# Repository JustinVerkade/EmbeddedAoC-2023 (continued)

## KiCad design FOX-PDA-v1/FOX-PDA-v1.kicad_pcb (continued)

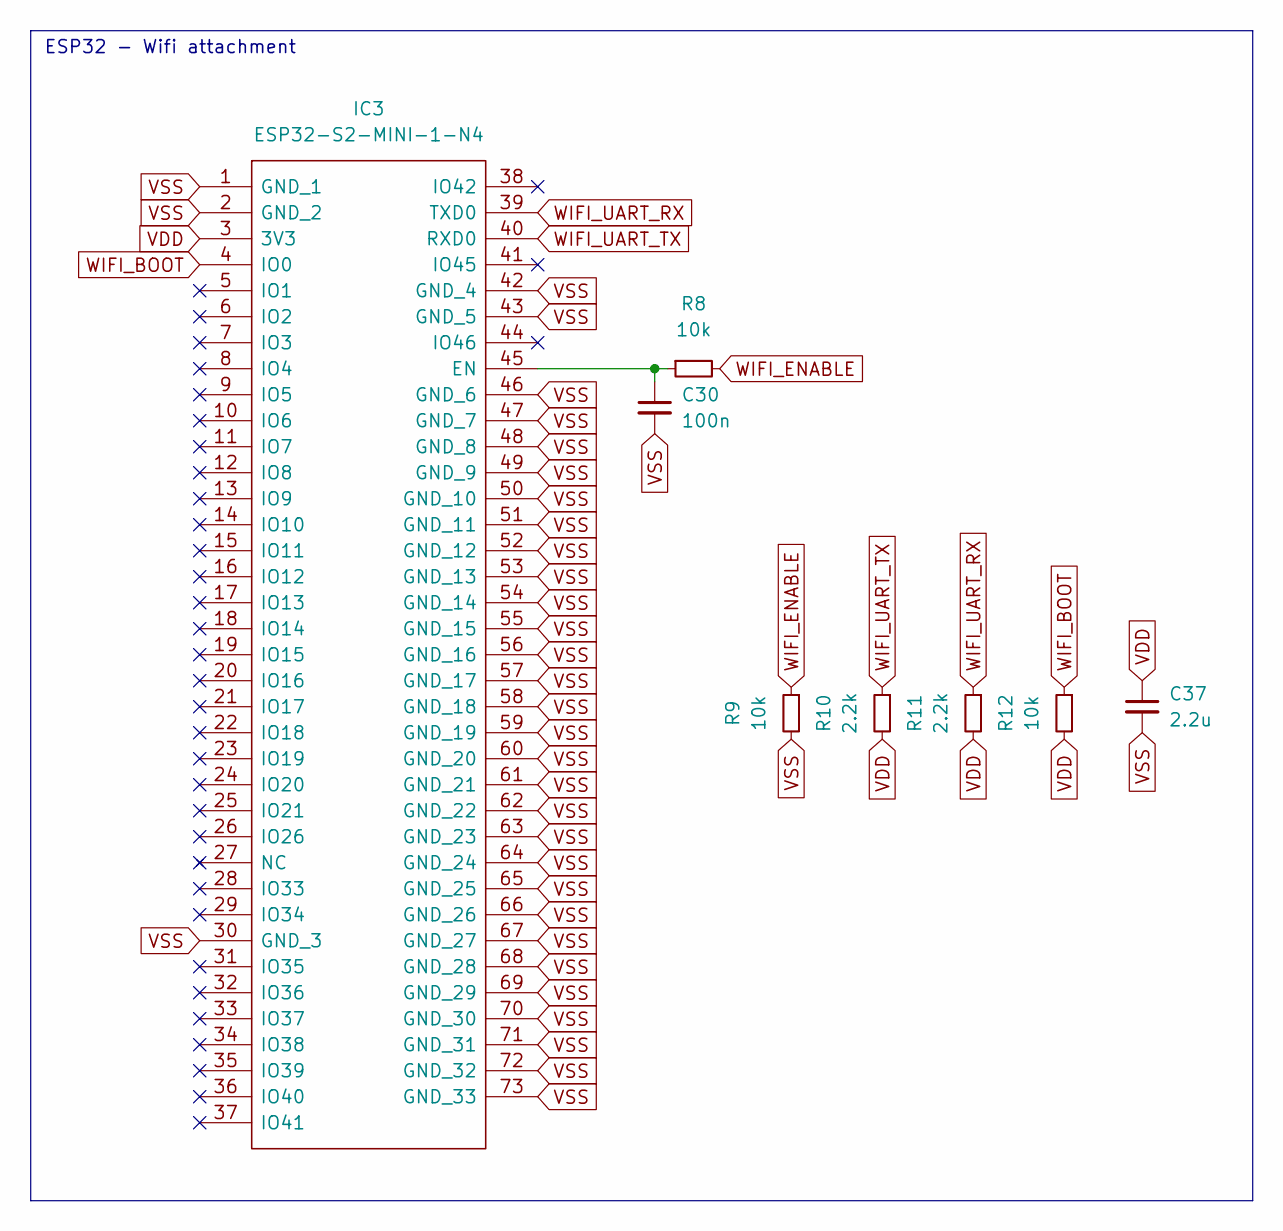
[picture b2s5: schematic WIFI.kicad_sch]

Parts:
C30: 100n; C_0402_1005Metric
C37: 2.2u; C_0603_1608Metric
IC3: ESP32-S2-MINI-1-N4; ESP32S2MINI1N4; Mouser Part Number 356-ESP32-S2-MINI-1
R8, R9, R12: 10k; R_0402_1005Metric
R10, R11: 2.2k; R_0402_1005Metric

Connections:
unnamed: C30.1, IC3.45 (EN), R8.1
VDD: C37.1, IC3.3 (3V3), R10.2, R11.2, R12.2; also elsewhere on the board
VSS: C30.2, C37.2, IC3.1 (GND_1), IC3.2 (GND_2), IC3.30 (GND_3), IC3.42 (GND_4), IC3.43 (GND_5), IC3.46 (GND_6), IC3.47 (GND_7), IC3.48 (GND_8), IC3.49 (GND_9), IC3.50 (GND_10), IC3.51 (GND_11), IC3.52 (GND_12), IC3.53 (GND_13), IC3.54 (GND_14), IC3.55 (GND_15), IC3.56 (GND_16), IC3.57 (GND_17), IC3.58 (GND_18), IC3.59 (GND_19), IC3.60 (GND_20), IC3.61 (GND_21), IC3.62 (GND_22), IC3.63 (GND_23), IC3.64 (GND_24), IC3.65 (GND_25), IC3.66 (GND_26), IC3.67 (GND_27), IC3.68 (GND_28), IC3.69 (GND_29), IC3.70 (GND_30), IC3.71 (GND_31), IC3.72 (GND_32), IC3.73 (GND_33), R9.2; also elsewhere on the board
WIFI_BOOT: IC3.4 (IO0), R12.1
WIFI_ENABLE: R8.2, R9.1; also elsewhere on the board
WIFI_UART_RX: IC3.39 (TXD0), R11.1; also elsewhere on the board
WIFI_UART_TX: IC3.40 (RXD0), R10.1; also elsewhere on the board

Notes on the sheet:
ESP32 - Wifi attachment

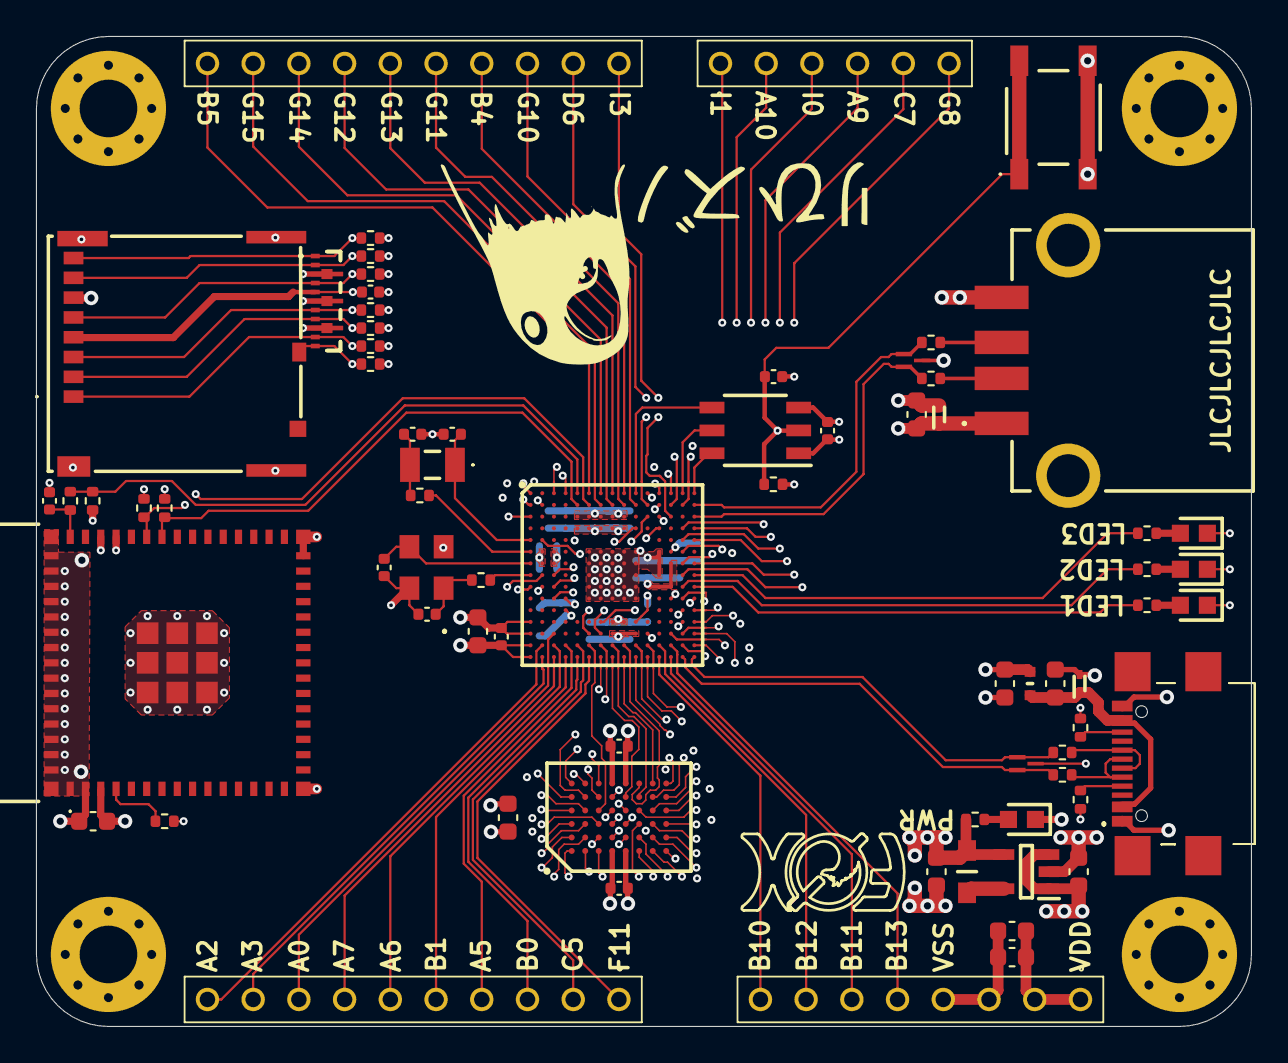
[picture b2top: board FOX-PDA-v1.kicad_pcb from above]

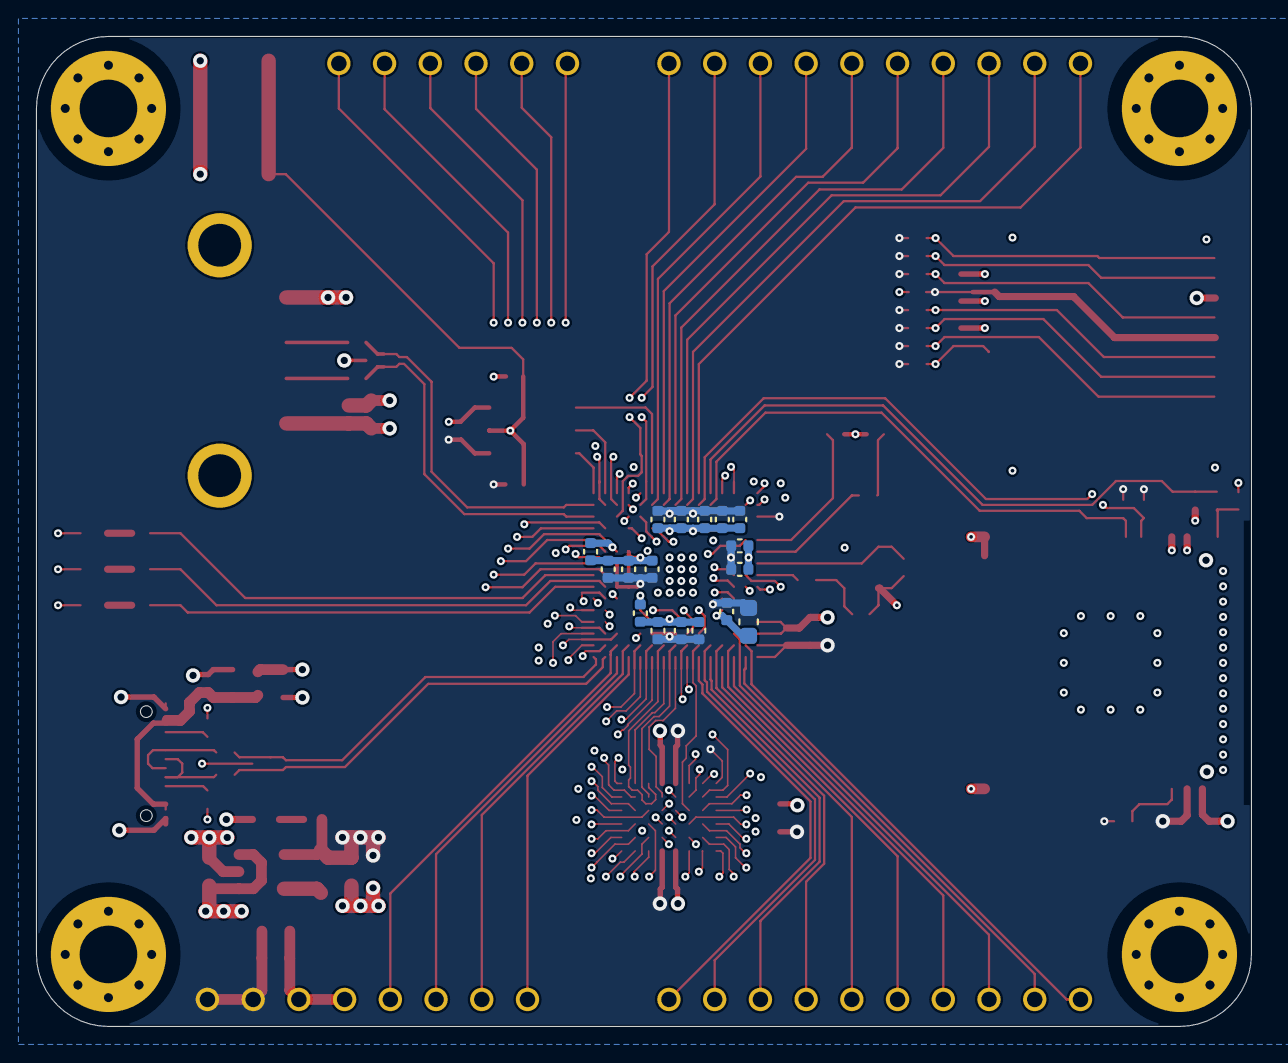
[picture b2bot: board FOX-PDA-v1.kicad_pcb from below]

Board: 6 copper layers, 67.5 x 55.0 mm, 93 parts (17 on the bottom side), 119 nets.

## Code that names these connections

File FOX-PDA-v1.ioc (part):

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Mcu.Name=STM32F745I(E-G)Kx
Mcu.Package=UFBGA176
Mcu.UserName=STM32F745IGKx
PA0/WKUP.Signal=ADCx_IN0
PA10.Signal=GPIO_Input
PA11.Mode=Host_Only
PA11.Signal=USB_OTG_FS_DM
PA12.Mode=Host_Only
PA12.Signal=USB_OTG_FS_DP
PA13.Mode=Trace_Asynchronous_SW
PA13.Signal=SYS_JTMS-SWDIO
PA14.Mode=Trace_Asynchronous_SW
PA14.Signal=SYS_JTCK-SWCLK
PA15.GPIOParameters=GPIO_Label
PA15.GPIO_Label=SDMMC_SW
PA15.Signal=GPIO_Input
PA2.Signal=ADCx_IN2
PA3.Signal=GPIO_Input
PA5.Signal=GPIO_Input
PA6.Signal=GPIO_Input
PA7.Signal=GPIO_Input
PA9.Signal=GPIO_Input
PB0.Signal=GPIO_Input
PB1.Signal=GPIO_Input
PB10.Signal=GPIO_Input
PB11.Signal=GPIO_Input
PB12.Signal=GPIO_Input
PB13.Signal=GPIO_Input
PB14.Mode=Device_Only_FS
PB14.Signal=USB_OTG_HS_DM
PB15.Mode=Device_Only_FS
PB15.Signal=USB_OTG_HS_DP
PB3.Mode=Trace_Asynchronous_SW
PB3.Signal=SYS_JTDO-SWO
PB4.Signal=GPIO_Input
PB5.Signal=GPIO_Input
PB6.GPIOParameters=GPIO_Label
PB6.GPIO_Label=WIFI_UART_TX
PB6.Mode=Asynchronous
PB6.Signal=USART1_TX
PB7.GPIOParameters=GPIO_Label
PB7.GPIO_Label=WIFI_UART_RX
PB7.Mode=Asynchronous
PB7.Signal=USART1_RX
PB8.GPIOParameters=GPIO_Label
PB8.GPIO_Label=WIFI_ENABLE
PB8.Signal=GPIO_Output
PC10.Signal=SDMMC1_D2
PC11.Signal=SDMMC1_D3
PC12.Mode=SD_1_bit
PC12.Signal=SDMMC1_CK
PC14/OSC32_IN.Mode=LSE-External-Oscillator
PC14/OSC32_IN.Signal=RCC_OSC32_IN
PC15/OSC32_OUT.Mode=LSE-External-Oscillator
PC15/OSC32_OUT.Signal=RCC_OSC32_OUT
PC5.Signal=GPIO_Input
PC6.GPIOParameters=GPIO_Label
PC6.GPIO_Label=LED3
PC6.Signal=GPIO_Output
PC7.Signal=GPIO_Input
PC8.Mode=SD_1_bit
PC8.Signal=SDMMC1_D0
PC9.Signal=SDMMC1_D1
PD0.Signal=FMC_D2_DA2
PD1.Signal=FMC_D3_DA3
PD10.Signal=FMC_D15_DA15
PD11.Signal=FMC_A16_CLE
PD12.Signal=FMC_A17_ALE
PD13.Signal=FMC_A18
PD14.Signal=FMC_D0_DA0
PD15.Signal=FMC_D1_DA1
PD2.Mode=SD_1_bit
PD2.Signal=SDMMC1_CMD
PD4.Signal=FMC_NOE
PD5.Signal=FMC_NWE
PD6.Signal=GPIO_Input
PD7.Mode=NorPsramChipSelect1_1
PD7.Signal=FMC_NE1
PD8.Signal=FMC_D13_DA13
PD9.Signal=FMC_D14_DA14
PE0.Signal=FMC_NBL0
PE1.Signal=FMC_NBL1
PE10.Signal=FMC_D7_DA7
PE11.Signal=FMC_D8_DA8
PE12.Signal=FMC_D9_DA9
PE13.Signal=FMC_D10_DA10
PE14.Signal=FMC_D11_DA11
PE15.Signal=FMC_D12_DA12
PE3.Signal=FMC_A19
PE4.Signal=FMC_A20
PE5.Signal=FMC_A21
PE7.Signal=FMC_D4_DA4
PE8.Signal=FMC_D5_DA5
PE9.Signal=FMC_D6_DA6
PF0.Signal=FMC_A0
PF1.Signal=FMC_A1
PF11.Signal=GPIO_Input
PF12.Signal=FMC_A6
PF13.Signal=FMC_A7
PF14.Signal=FMC_A8
PF15.Signal=FMC_A9
PF2.Signal=FMC_A2
PF3.Signal=FMC_A3
PF4.Signal=FMC_A4
PF5.Signal=FMC_A5
PF7.GPIOParameters=GPIO_Label
PF7.GPIO_Label=STATUS_LED
PF7.Signal=S_TIM11_CH1
PG0.Signal=FMC_A10
PG1.Signal=FMC_A11
PG10.Signal=GPIO_Input
PG11.Signal=GPIO_Input
PG12.Signal=GPIO_Input
PG13.Signal=GPIO_Input
PG14.Signal=GPIO_Input
PG15.Signal=GPIO_Input
PG2.Signal=FMC_A12
PG3.Signal=FMC_A13
PG4.Signal=FMC_A14_BA0
PG5.Signal=FMC_A15_BA1
PG6.GPIOParameters=GPIO_Label
PG6.GPIO_Label=LED1
PG6.Signal=GPIO_Output
PG7.GPIOParameters=GPIO_Label
PG7.GPIO_Label=LED2
PG7.Signal=GPIO_Output
PG8.Signal=GPIO_Input
PH0/OSC_IN.Mode=HSE-External-Oscillator
PH0/OSC_IN.Signal=RCC_OSC_IN
PH1/OSC_OUT.Mode=HSE-External-Oscillator
PH1/OSC_OUT.Signal=RCC_OSC_OUT
PI0.Signal=GPIO_Input
PI1.Signal=GPIO_Input
PI2.GPIOParameters=GPIO_Label
PI2.GPIO_Label=USB_HOST_VBUF
PI2.Signal=GPIO_Output
PI3.Signal=GPIO_Input
RCC.HSE_VALUE=16000000
RCC.SYSCLKFreq_VALUE=216000000
RCC.SYSCLKSource=RCC_SYSCLKSOURCE_PLLCLK
board=custom

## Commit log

2023-07-14 Added f_debug call for FatFs debug logging
2023-07-14 Fixed readme line spacing issue
2023-07-15 Added system check at startup with error handler implementation
2023-08-03 General update
2023-08-09 Added AoC structure
2023-08-09 Add image
2023-11-15 Updated to serial controlled'
2023-11-17 Added more serial interface features to off load some steps during the event
2023-11-30 SRAM update
2023-12-04 Days 1-4
2023-12-12 Day x -> Day 12
2023-12-14 Day 14
2023-12-15 Day 15
2024-03-12 Added hardware files
2024-08-17 Updated last event of code data.
